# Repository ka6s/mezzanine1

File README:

This is a small 5V power supply that can be added to the existing RP_ADAPTER.

It uses Anderson Power Poles to receive 12V. These being modular -they can be connected to the 
existing power connection of the rp_adapter.  This was created to power the Raspberry Pi.

There are two USB connectors and a 13.8V fan connection available.

This is a total rip-off of the LPU 5V section of provided by OpenHPSDR and all credit goes to them,
all blame for layout issues goes to me.

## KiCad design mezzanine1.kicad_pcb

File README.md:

Mezzanine1

This is a small 5V power supply that can be added to the existing RP_ADAPTER.

It uses Anderson Power Poles to receive 12V. These being modular -they can be connected to the 
existing power connection of the rp_adapter.  This was created to power the Raspberry Pi.

There are two USB connectors and a 13.8V fan connection available.

This is a total rip-off of the LPU 5V section of provided by OpenHPSDR and all credit goes to them,
all blame for layout issues goes to me.

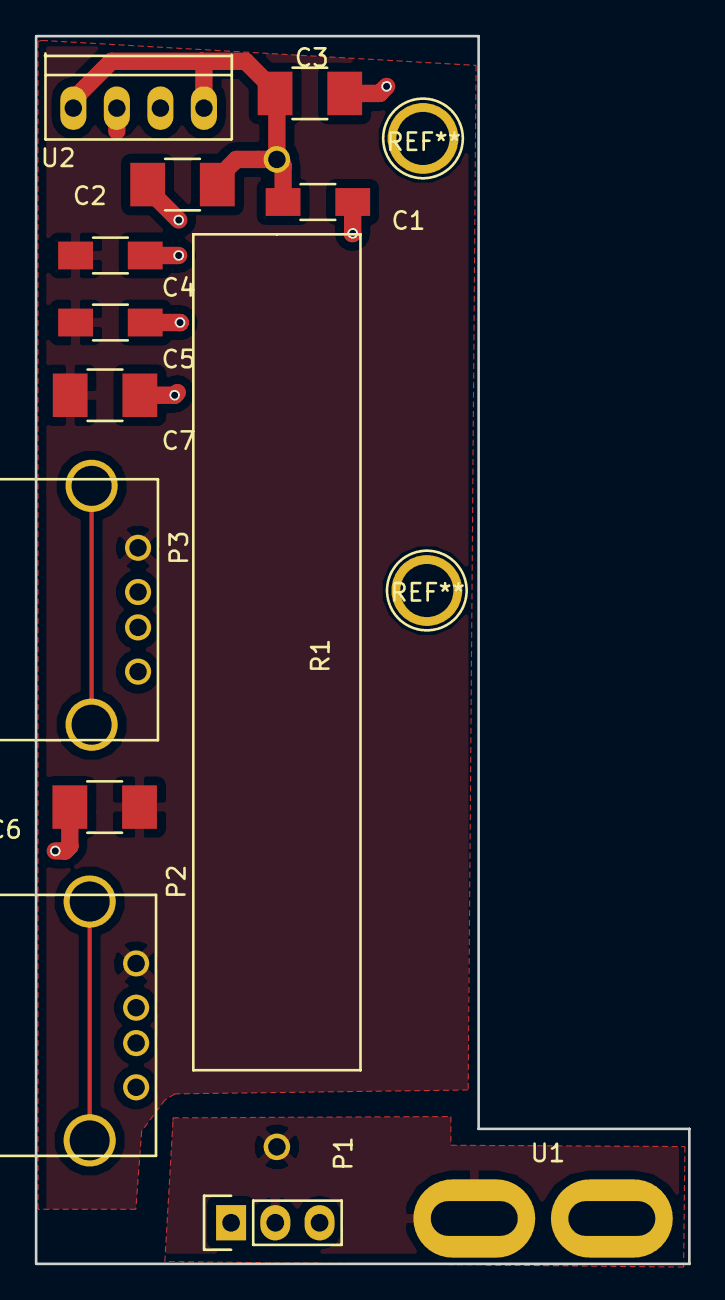
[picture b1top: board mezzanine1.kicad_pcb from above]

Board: 2 copper layers, 37.5 x 70.5 mm, 13 parts (0 on the bottom side), 4 nets.

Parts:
C1, C4: 0.1uF; C_1206_HandSoldering
C2: 1uF; C_1210_HandSoldering
C3, C6, C7: 100uF; C_1210_HandSoldering
C5: 1uF; C_1206_HandSoldering
P1: CONN_01X03; Pin_Header_Straight_1x03
P2, P3: USB_A
R1: 2.2; RES_10W
U1: PwrPole; RA_POWER_POLE
U2: KA278R05; TO-220_4pin_vertical

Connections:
GND: C1.2, C2.2, C3.2, C4.2, C5.2, C6.2, C7.2, P1.1, P2.4, P3.4, U1.1, U2.3
unnamed: C1.1, C2.1, C3.1, R1.1, U2.1, U2.4
unnamed: C4.1, C5.1, C6.1, C7.1, P2.1, P3.1, U2.2
unnamed: P1.2, R1.2, U1.2

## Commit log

2016-11-03 Update BOM
